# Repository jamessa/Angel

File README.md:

# Angel (2021)

Hand wired QMK is almost ready.  https://github.com/qmk/qmk_firmware/pull/11501

A symmetric staggered ergonomic keyboard.

## Idea

A slightly ergonomic keyboard that fits into 60% form factor.  

 ## Featuring

* Staggered yet ergonmic 

* Maximize hand distance 

* Arrow keys are must.

* Fitts' law is respected. Four corner keys are maximized while [you shall no call its name] is break into 3 keys.  The gaint space bar is a huge waste ot thumb(s). It breaks into 1.25, 1.5, 1.25 to free it up. My favorite combination is, <kbd>backspace</kbd>, <kbd>enter</kbd>, <kbd>whitespace</kbd>.

* 60% form factor which should fix your notebook perfectly.

* all keys are under 1.75u which means no stablizer is required. Period.

##  Cons

It's incompatible to traditioal keycaps layout. **CAPS LOCK** is the only 1.75u key on traditional keyboard. In Symmetric 60%, 4 is required but you can always swap into smaller keycaps at your wish.

## Prior work

in the order of first appearance.

[Symmetric Stagger 60%]( https://geekhack.org/index.php?topic=66965.0)  by Jesse Vincent, Keyboardio  While I wait for the Model 01 boards to come back from Shenzhen, I've been messing around with a symmetric stagger 60% layout. Before I go and get 5 PCBs made, I'd love layout feedback from folks.

### Meti
[SemiErgo](https://github.com/mtei/SemiErgo_Layout) by meti (March 2017)    I will vote it for ANSI standard without any doubt.

[Symmetric 70 hand-wire](https://github.com/qmk/qmk_firmware/tree/master/keyboards/handwired/symmetric70_proto) (2020)

### Rominronin
[Katana 60](https://deskthority.net/viewtopic.php?t=16287&start=30) (Nov, 2017). it's a beauty.  ps. the character in the middle is 刀 which means sword in Chinese and Japanese.

[Tsuka60 - the Katana60 v2 PCB interest check](https://geekhack.org/index.php?topic=100468.msg2756587#msg2756587) (2019)

[Candykeys](https://candykeys.com/product/katana60-pcb-V2) (2020)

## Next

Now I am going to handwire one to refuse my point. Stay tune.

You can [try it on paper](try_it.pdf) and [let me know](https://forms.gle/i4KZJjDPFTidD8Jt6) how to you think about Symmetric60.

## References

On space bar http://xahlee.info/kbd/keyboard_problems.html

Key symbols from http://xahlee.info/comp/unicode_computing_symbols.html

Mac keyboard shortcuts https://support.apple.com/en-us/HT201236

Human Engineering the Keyboard by K. H. Eberhard Kroemer
 Human Factors: The Journal of the Human Factors and Ergonomics Society 1972 14: 51 DOI: [10.1177/001872087201400110](
http://hfs.sagepub.com/content/14/1/51)

## Prototyping Tips

### Kicad

  - Hardware acceleration will eeschema freezes, so don't enable it. Reset settings by `rm -rf ~/Library/Preferences/kicad` or verisioning it.
  - Plot gerber files and drills based on [JCLPCB's tutorial](https://support.jlcpcb.com/article/102-kicad-515---generating-gerber-and-drill-files). [Suggested naming patterns](https://support.jlcpcb.com/article/29-suggested-naming-patterns)

Special thanks to Haway 梁, Jeff 邱, Justin 吳.

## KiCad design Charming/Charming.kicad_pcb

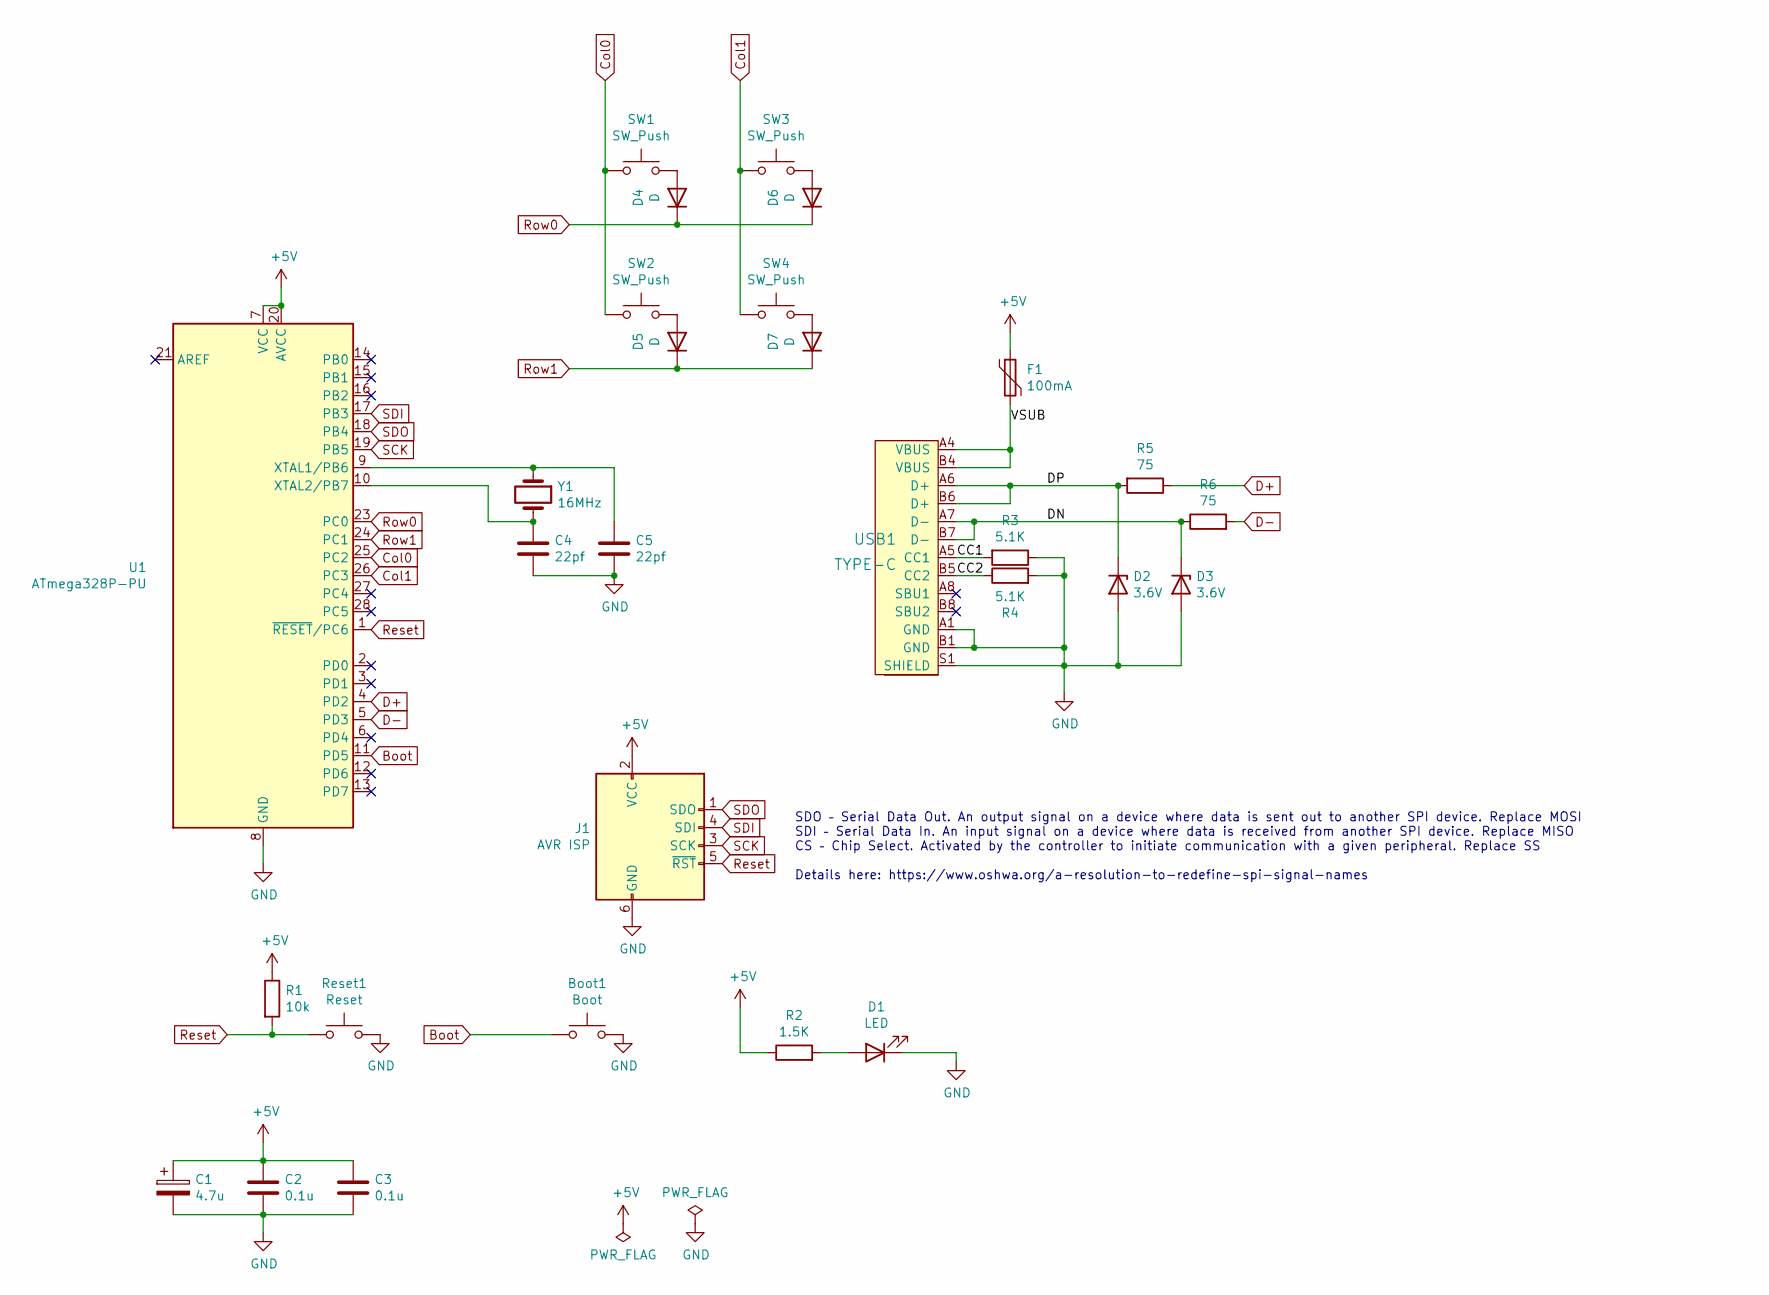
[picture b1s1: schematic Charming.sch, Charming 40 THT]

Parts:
Boot1: Boot; SW_PUSH_6mm
C1: 4.7u; CP_Radial_D4.0mm_P1.50mm
C2, C3: 0.1u; C_Disc_D4.3mm_W1.9mm_P5.00mm
C4, C5: 22pf; C_Disc_D3.0mm_W1.6mm_P2.50mm
D1: LED; LED_D3.0mm
D2, D3: 3.6V; D_DO-35_SOD27_P7.62mm_Horizontal
D4, D5, D6, D7: D; D_DO-35_SOD27_P7.62mm_Horizontal
F1: 100mA; Fuse_Bourns_MF-RG500
J1: AVR ISP; AVRISP
R1: 10k; R_Axial_DIN0204_L3.6mm_D1.6mm_P5.08mm_Horizontal
R2: 1.5K; R_Axial_DIN0204_L3.6mm_D1.6mm_P5.08mm_Horizontal
R3, R4: 5.1K; R_Axial_DIN0204_L3.6mm_D1.6mm_P5.08mm_Horizontal
R5, R6: 75; R_Axial_DIN0204_L3.6mm_D1.6mm_P5.08mm_Horizontal
Reset1: Reset; SW_PUSH_6mm
SW1, SW2, SW3, SW4: SW_Push; SW_Cherry_MX_1.00u_PCB
U1: ATmega328P-PU; DIP-28_W7.62mm
USB1: TYPE-C; USB_C_Receptacle_HRO_TYPE-C-31-M-12
Y1: 16MHz; Crystal_HC49-4H_Vertical

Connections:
+5V: C1.1, C2.1, C3.1, F1.1, J1.2 (VCC), R1.1, R2.1, U1.7 (VCC), U1.20 (AVCC)
/CC1: R3.2, USB1.A5 (CC1)
/CC2: R4.1, USB1.B5 (CC2)
/DN: D3.1 (K), R6.1, USB1.A7 (D-), USB1.B7 (D-)
/DP: D2.1 (K), R5.2, USB1.A6 (D+), USB1.B6 (D+)
/VSUB: F1.2, USB1.A4 (VBUS), USB1.B4 (VBUS)
Boot: Boot1.1, U1.11 (PD5)
Col0: SW1.1, SW2.1, U1.25 (PC2)
Col1: SW3.1, SW4.1, U1.26 (PC3)
D+: R5.1, U1.4 (PD2)
D-: R6.2, U1.5 (PD3)
GND: Boot1.2, C1.2, C2.2, C3.2, C4.1, C5.1, D1.1 (K), D2.2 (A), D3.2 (A), J1.6 (GND), R3.1, R4.2, Reset1.2, U1.8 (GND), U1.22 (GND), USB1.A1 (GND), USB1.B1 (GND), USB1.S1 (SHIELD)
unnamed: C4.2, U1.10 (XTAL2/PB7), Y1.2
unnamed: C5.2, U1.9 (XTAL1/PB6), Y1.1
unnamed: D1.2 (A), R2.2
unnamed: D4.2 (A), SW1.2
unnamed: D5.2 (A), SW2.2
unnamed: D6.2 (A), SW3.2
unnamed: D7.2 (A), SW4.2
Reset: J1.5 (~RST), R1.2, Reset1.1, U1.1 (~RESET~/PC6)
Row0: D4.1 (K), D6.1 (K), U1.23 (PC0)
Row1: D5.1 (K), D7.1 (K), U1.24 (PC1)
SCK: J1.3 (SCK), U1.19 (PB5)
SDI: J1.4 (SDI), U1.17 (PB3)
SDO: J1.1 (SDO), U1.18 (PB4)

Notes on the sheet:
SDO – Serial Data Out. An output signal on a device where data is sent out to another SPI device. Replace MOSI SDI – Serial Data In. An input signal on a device where data is received from another SPI device. Replace MISO CS – Chip Select. Activated by the controller to initiate communication with 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

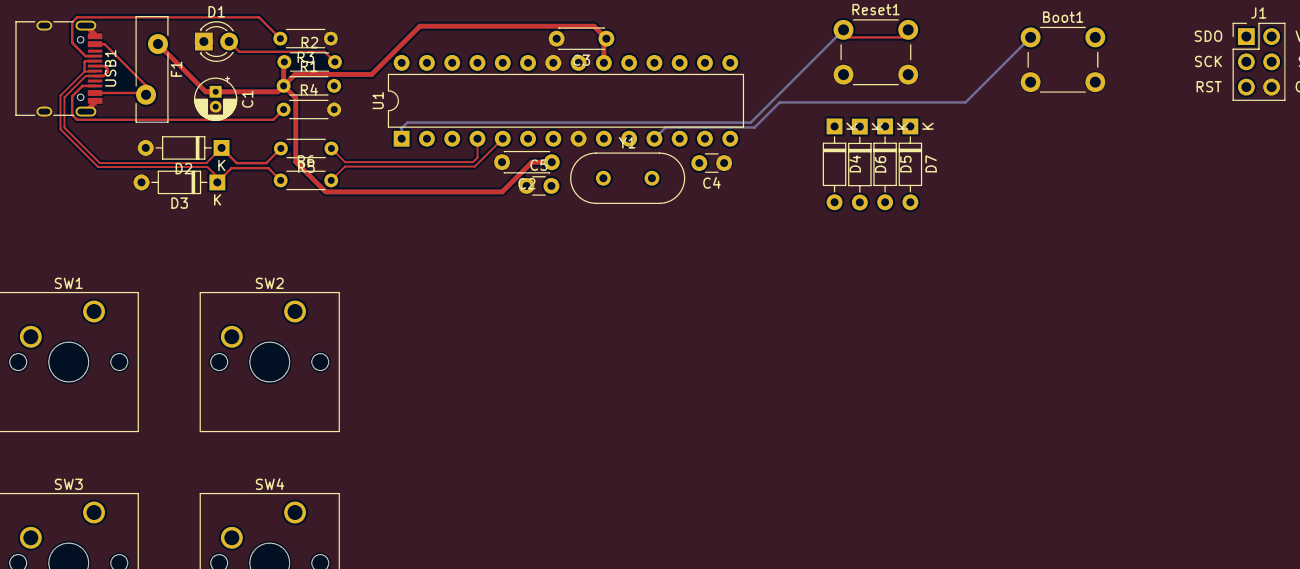
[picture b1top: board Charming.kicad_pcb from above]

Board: 2 copper layers, 29 parts (0 on the bottom side), 25 nets.

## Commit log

2020-02-02 Palinedrome day 20200202
2020-02-02 fix format
2020-02-02 readme you must
2020-02-02 no space it is
2020-02-02 more contrast
2020-02-02 feedback form
2020-02-03 plate
2020-02-03 try it
2020-02-25 fix template resolution
2020-06-16 schematic
2020-06-16 sym4
2020-06-17 keyboard matrix ok
2020-06-17 all components on but routing failed
2020-06-17 3d view is back
2020-06-17 update PG13500 footprint
2020-06-17 before row col changle
2020-06-17 add switch and promicro courtyard
2020-06-18 update output file
2020-06-20 change diode connector position
2020-06-20 nice and clean signal lines
2020-06-21 bring back DRC by providing courtyard
2020-06-22 even odd pins
2020-06-22 export new gerber
2020-06-23 cleanup
2020-07-15 Kicad routing practice
2020-07-15 bump
2020-07-31 new layout
2020-08-04 customize symbol and footprint
2020-08-05 add 3D model
2020-08-05 power first design
2020-08-10 name netlist
2020-08-25 move customize footprints to external libs
2021-01-10 Angel is born
2021-01-10 fix keyboard path
2021-01-10 add prior updates
2021-01-11 graphics
2021-01-27 Add QMK status
2021-01-27 don't try to be fancy
